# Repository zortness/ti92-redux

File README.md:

# TI-92 Redux
Bringing the TI-92's back to life.

## Intro
My first graphing calculator and introduction to portable programming was an early TI-85.
I became enamoured with the TI calculators in the 90s, longing for a TI-92 when they were
announced, but never able to purchase one. Now, you can find them in various conditions for
relatively cheap on the internet.

Unfortunately, the most common issues seem to be screen related, and the screens on the TI-92
are not easily repaired. Such was the case with one of the TI-92s I purchased, so I began 
thinking about how I could make use of this iconic chasis. 

I found other projects, notably one seen on Hackaday, the 
[TI-92 Revive project](https://hackaday.io/project/175448-reviving-the-ti-92-calculator-into-a-rpi-pc)
and corresponding [github repo](https://github.com/ccadic/TI92-revive). 
This is a cool project in a similar vein, but I wanted to make some different design decisions.

* First, I wanted the PCB to be as simple as possible for the first attempt, trying to keep to a 
2-layer board. 
* Second, I wanted to have the keyboard to be operable as a standalone unit, in case someone wanted
to use it on another project or different SBC than I chose.
* Third, I wanted to re-use as much of the original TI-92 chasis as possible. A goal which I didn't
meet to the original expectation due to the complexity of the original back plates. 

## Physical Replication Strategy
For several parts of this build, I traced the original components (PCB, back plate, etc) onto a 
piece of paper, then scanned them with a flat bed scanner. I then took the drawings and traced 
them into SVG's set to the correct dimensions using InkScape so I could use them with other tools 
such as KiCad and OpenSCAD. I also printed multiple versions of the PCB and various chasis bits 
on my 3D printer to work toward getting the correct fitment with the original chasis pieces.

Most of the SVGs and drawings are included [here](drawings/).

## PCB Design
The PCB is designed in KiCad 7. The board is designed as a custom keyboard, using a Pi Pico (or Pico W)
as the keybord controller. The routing is all done by hand with an attempt at keeping the jumps minimal.

Note: The PCB has tabs and holes to hold an SBC that lines up with the Raspberry Pi mounting holes.

### BOM And Assembly
* 80 count SOD-123 general purpose diode, [1N4148W-TP](https://www.digikey.com/en/products/detail/micro-commercial-co/1N4148W-TP/717196)
* 1 count [RS-282G05A3 tactile switch](https://www.digikey.com/en/products/detail/c-k/RS-282G05A3-SM-RT/2747190)
* 1 count [Pi Pico W](https://www.digikey.com/en/products/detail/raspberry-pi/SC0918/16608263)

I was able to solder all of this with a relatively large soldering iron and some tweezers.
Tin one of the pads for the component first, then heat it up again and set the part on the pad.
Only solder the second pad when you're happy with the alignment.

I used a Raspberry Pi 4 as my SBC.

To pair with the Pi 4, I used the [Pimoroni Hyperpixel 4.0" Touch Display](https://www.adafruit.com/product/3578).
This display is pretty expensive, but I purchased this a while ago, and noticing it seemed to fit perfectly
into the TI-92 chasis is one of the factors that pushed me into completing this project.

A 4" screen of this ratio fits almost perfectly into the TI-92. 

## Printed Pieces
I used OpenSCAD to assemble the designs for printing. Most of the prints are derived from one or 
more SVG drawings, the back plate being the most complicated.

During development, I dropped my keyboard and had to chase keys across the house multiple times. 
I ultimately ended up finding all of my keys, but there is a basic key file included in case you
need to print one.

## Keyboard Software
I chose the [KMK firmware](https://github.com/KMKfw/kmk_firmware) 
(as opposed to something like [QMK](https://docs.qmk.fm/#/) ) mostly due to ease of use and direct
support for the Pi Pico and Pico W. This has the added bonus of being able to easily reprogram the 
keyboard from the finished device itself, using the keyboard itself to make changes.

Follow the instructions for installing the KMK firmware on the device (basically copy most of the
files included in their release). Then drag and drop the [firmware/code.py](firmware/code.py) file
onto the device and it should be ready to go.

## Power Supply
There is no power supply built into this project. For my personal prototype, I'm using a 
[2x18650 container](https://www.digikey.com/en/products/detail/seeed-technology-co-ltd/114090053/10451921)
with a built-in on/off switch into a cheap buck converter. I also attempted to use a L7805 5V
linear regulator, and while it works, even with a heat sink it will get very hot.

I am currently powering the Pi Pico W through the USB cable that connects it to the Pi 4. 

## Development Software
* [KiCad 7](https://www.kicad.org/)
* [InkScape 1.2](https://inkscape.org/)
* [OpenSCAD](http://openscad.org/)
* [KMK Firmware](https://github.com/KMKfw/kmk_firmware)

## Version History

### 2023-05-19 Rev 0
* PCB Rev 0 - Functional 
  * Some mounting hole misalignments that need to be fixed by hand
* KMK Keyboard Firmware - Functional
  * Will work as a USB keyboard on any modern PC
  * Some QoL improvements need to be made on the mouse functionality
  * Really need BlueTooth support to eliminate the USB cable
* Back Plate - Functional
  * Very basic, you can tape or glue power sources to it if so inclined

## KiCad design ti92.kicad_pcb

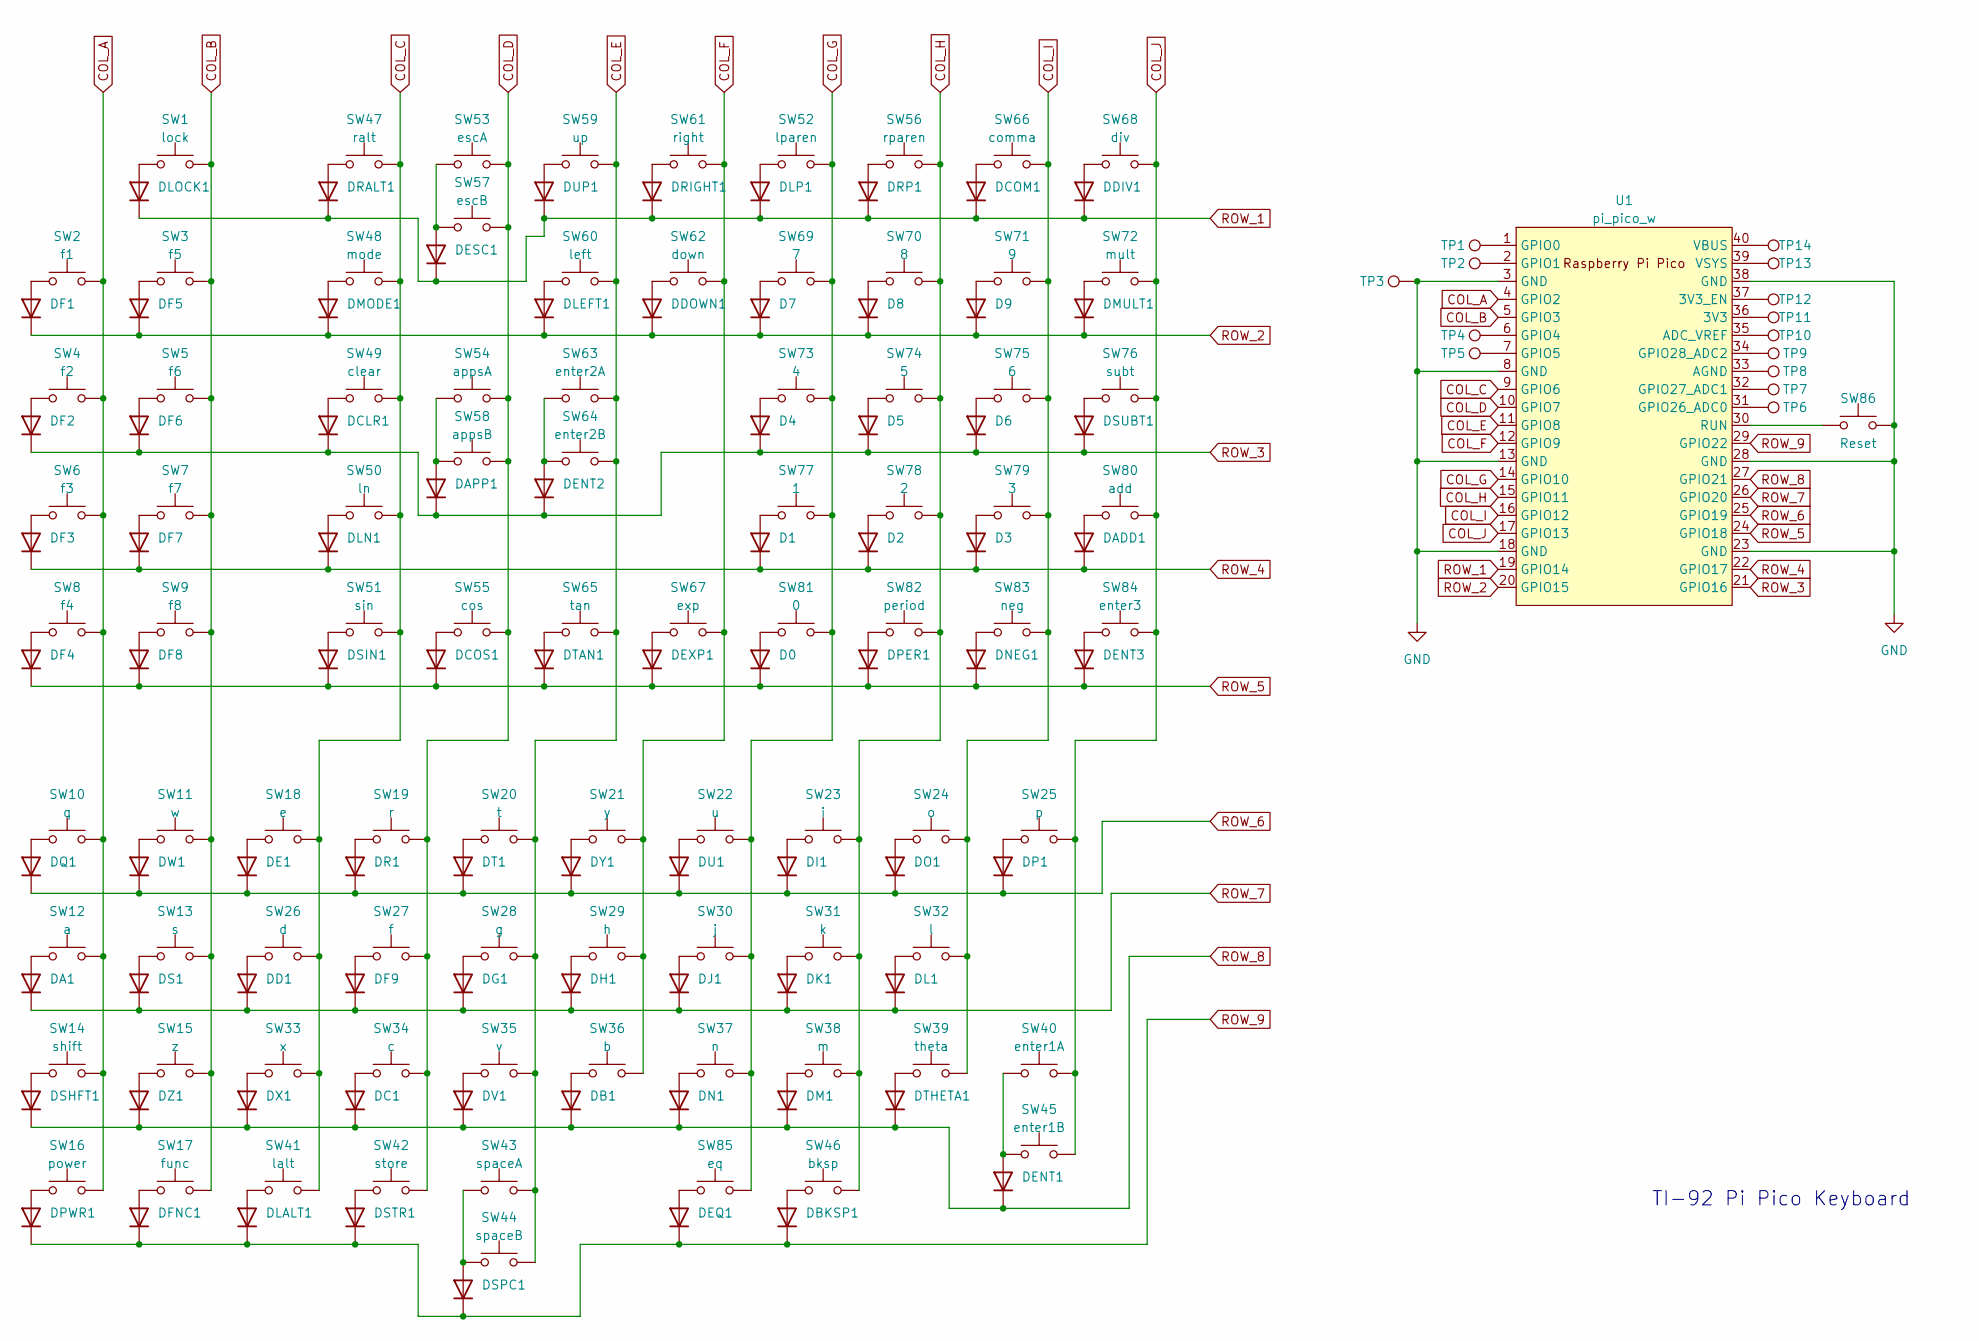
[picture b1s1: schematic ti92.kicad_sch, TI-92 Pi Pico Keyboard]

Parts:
D0, D1, D2, D3, D4, D5, D6, D7, D8, D9: 1N4148W; D_SOD-123
DA1: 1N4148W; D_SOD-123
DADD1: 1N4148W; D_SOD-123
DAPP1: 1N4148W; D_SOD-123
DB1: 1N4148W; D_SOD-123
DBKSP1: 1N4148W; D_SOD-123
DC1: 1N4148W; D_SOD-123
DCLR1: 1N4148W; D_SOD-123
DCOM1: 1N4148W; D_SOD-123
DCOS1: 1N4148W; D_SOD-123
DD1: 1N4148W; D_SOD-123
DDIV1: 1N4148W; D_SOD-123
DDOWN1: 1N4148W; D_SOD-123
DE1: 1N4148W; D_SOD-123
DENT1, DENT2, DENT3: 1N4148W; D_SOD-123
DEQ1: 1N4148W; D_SOD-123
DESC1: 1N4148W; D_SOD-123
DEXP1: 1N4148W; D_SOD-123
DF1, DF2, DF3, DF4, DF5, DF6, DF7, DF8, DF9: 1N4148W; D_SOD-123
DFNC1: 1N4148W; D_SOD-123
DG1: 1N4148W; D_SOD-123
DH1: 1N4148W; D_SOD-123
DI1: 1N4148W; D_SOD-123
DJ1: 1N4148W; D_SOD-123
DK1: 1N4148W; D_SOD-123
DL1: 1N4148W; D_SOD-123
DLALT1: 1N4148W; D_SOD-123
DLEFT1: 1N4148W; D_SOD-123
DLN1: 1N4148W; D_SOD-123
DLOCK1: 1N4148W; D_SOD-123
DLP1: 1N4148W; D_SOD-123
DM1: 1N4148W; D_SOD-123
DMODE1: 1N4148W; D_SOD-123
DMULT1: 1N4148W; D_SOD-123
DN1: 1N4148W; D_SOD-123
DNEG1: 1N4148W; D_SOD-123
DO1: 1N4148W; D_SOD-123
DP1: 1N4148W; D_SOD-123
DPER1: 1N4148W; D_SOD-123
DPWR1: 1N4148W; D_SOD-123
DQ1: 1N4148W; D_SOD-123
DR1: 1N4148W; D_SOD-123
DRALT1: 1N4148W; D_SOD-123
DRIGHT1: 1N4148W; D_SOD-123
DRP1: 1N4148W; D_SOD-123
DS1: 1N4148W; D_SOD-123
DSHFT1: 1N4148W; D_SOD-123
DSIN1: 1N4148W; D_SOD-123
DSPC1: 1N4148W; D_SOD-123
DSTR1: 1N4148W; D_SOD-123
DSUBT1: 1N4148W; D_SOD-123
DT1: 1N4148W; D_SOD-123
DTAN1: 1N4148W; D_SOD-123
DTHETA1: 1N4148W; D_SOD-123
DU1: 1N4148W; D_SOD-123
DUP1: 1N4148W; D_SOD-123
DV1: 1N4148W; D_SOD-123
DW1: 1N4148W; D_SOD-123
DX1: 1N4148W; D_SOD-123
DY1: 1N4148W; D_SOD-123
DZ1: 1N4148W; D_SOD-123
SW1: lock; tibuttonpad
SW2: f1; tibuttonpad
SW3: f5; tibuttonpad
SW4: f2; tibuttonpad
SW5: f6; tibuttonpad
SW6: f3; tibuttonpad
SW7: f7; tibuttonpad
SW8: f4; tibuttonpad
SW9: f8; tibuttonpad
SW10: q; tibuttonpad
SW11: w; tibuttonpad
SW12: a; tibuttonpad
SW13: s; tibuttonpad
SW14: shift; tibuttonpad
SW15: z; tibuttonpad
SW16: power; tibuttonpad
SW17: func; tibuttonpad
SW18: e; tibuttonpad
SW19: r; tibuttonpad
SW20: t; tibuttonpad
SW21: y; tibuttonpad
SW22: u; tibuttonpad
SW23: i; tibuttonpad
SW24: o; tibuttonpad
SW25: p; tibuttonpad
SW26: d; tibuttonpad
SW27: f; tibuttonpad
SW28: g; tibuttonpad
SW29: h; tibuttonpad
SW30: j; tibuttonpad
SW31: k; tibuttonpad
SW32: l; tibuttonpad
SW33: x; tibuttonpad
SW34: c; tibuttonpad
SW35: v; tibuttonpad
SW36: b; tibuttonpad
SW37: n; tibuttonpad
SW38: m; tibuttonpad
SW39: theta; tibuttonpad
SW40: enter1A; tibuttonpad
SW41: lalt; tibuttonpad
SW42: store; tibuttonpad
SW43: spaceA; tibuttonpad
SW44: spaceB; tibuttonpad
SW45: enter1B; tibuttonpad
SW46: bksp; tibuttonpad
SW47: ralt; tibuttonpad
SW48: mode; tibuttonpad
SW49: clear; tibuttonpad
SW50: ln; tibuttonpad
SW51: sin; tibuttonpad
SW52: lparen; tibuttonpad
SW53: escA; tibuttonpad
SW54: appsA; tibuttonpad
SW55: cos; tibuttonpad
SW56: rparen; tibuttonpad
SW57: escB; tibuttonpad
SW58: appsB; tibuttonpad
SW59: up; tibuttonpad
SW60: left; tibuttonpad
SW61: right; tibuttonpad
SW62: down; tibuttonpad
SW63: enter2A; tibuttonpad
SW64: enter2B; tibuttonpad
SW65: tan; tibuttonpad
SW66: comma; tibuttonpad
SW67: exp; tibuttonpad
SW68: div; tibuttonpad
SW69: 7; tibuttonpad
SW70: 8; tibuttonpad
SW71: 9; tibuttonpad
SW72: mult; tibuttonpad
SW73: 4; tibuttonpad
SW74: 5; tibuttonpad
SW75: 6; tibuttonpad
SW76: subt; tibuttonpad
SW77: 1; tibuttonpad
SW78: 2; tibuttonpad
SW79: 3; tibuttonpad
SW80: add; tibuttonpad
SW81: 0; tibuttonpad
SW82: period; tibuttonpad
SW83: neg; tibuttonpad
SW84: enter3; tibuttonpad
SW85: eq; tibuttonpad
SW86: Reset; SW_SPST_CK_RS282G05A3
TP1, TP2, TP3, TP4, TP5, TP6, TP7, TP8, TP9, TP10, TP11, TP12, TP13, TP14: TestPoint_Pad_D1.5mm
U1: pi_pico_w

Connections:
COL_A: SW2.2, SW4.2, SW6.2, SW8.2, SW10.2, SW12.2, SW14.2, SW16.2, U1.4 (GPIO2)
COL_B: SW1.2, SW3.2, SW5.2, SW7.2, SW9.2, SW11.2, SW13.2, SW15.2, SW17.2, U1.5 (GPIO3)
COL_C: SW18.2, SW26.2, SW33.2, SW41.2, SW47.2, SW48.2, SW49.2, SW50.2, SW51.2, U1.9 (GPIO6)
COL_D: SW19.2, SW27.2, SW34.2, SW42.2, SW53.2, SW54.2, SW55.2, SW57.2, SW58.2, U1.10 (GPIO7)
COL_E: SW20.2, SW28.2, SW35.2, SW43.2, SW44.2, SW59.2, SW60.2, SW63.2, SW64.2, SW65.2, U1.11 (GPIO8)
COL_F: SW21.2, SW29.2, SW36.2, SW61.2, SW62.2, SW67.2, U1.12 (GPIO9)
COL_G: SW22.2, SW30.2, SW37.2, SW52.2, SW69.2, SW73.2, SW77.2, SW81.2, SW85.2, U1.14 (GPIO10)
COL_H: SW23.2, SW31.2, SW38.2, SW46.2, SW56.2, SW70.2, SW74.2, SW78.2, SW82.2, U1.15 (GPIO11)
COL_I: SW24.2, SW32.2, SW39.2, SW66.2, SW71.2, SW75.2, SW79.2, SW83.2, U1.16 (GPIO12)
COL_J: SW25.2, SW40.2, SW45.2, SW68.2, SW72.2, SW76.2, SW80.2, SW84.2, U1.17 (GPIO13)
GND: SW86.2, TP3.1, U1.3 (GND), U1.8 (GND), U1.13 (GND), U1.18 (GND), U1.23 (GND), U1.28 (GND), U1.38 (GND)
unnamed: D0.2 (A), SW81.1
unnamed: D1.2 (A), SW77.1
unnamed: D2.2 (A), SW78.1
unnamed: D3.2 (A), SW79.1
unnamed: D4.2 (A), SW73.1
unnamed: D5.2 (A), SW74.1
unnamed: D6.2 (A), SW75.1
unnamed: D7.2 (A), SW69.1
unnamed: D8.2 (A), SW70.1
unnamed: D9.2 (A), SW71.1
unnamed: DA1.2 (A), SW12.1
unnamed: DADD1.2 (A), SW80.1
unnamed: DAPP1.2 (A), SW54.1, SW58.1
unnamed: DB1.2 (A), SW36.1
unnamed: DBKSP1.2 (A), SW46.1
unnamed: DC1.2 (A), SW34.1
unnamed: DCLR1.2 (A), SW49.1
unnamed: DCOM1.2 (A), SW66.1
unnamed: DCOS1.2 (A), SW55.1
unnamed: DD1.2 (A), SW26.1
unnamed: DDIV1.2 (A), SW68.1
unnamed: DDOWN1.2 (A), SW62.1
unnamed: DENT1.2 (A), SW40.1, SW45.1
unnamed: DENT2.2 (A), SW63.1, SW64.1
unnamed: DENT3.2 (A), SW84.1
unnamed: DEQ1.2 (A), SW85.1
unnamed: DESC1.2 (A), SW53.1, SW57.1
unnamed: DEXP1.2 (A), SW67.1
unnamed: DF1.2 (A), SW2.1
unnamed: DF2.2 (A), SW4.1
unnamed: DF3.2 (A), SW6.1
unnamed: DF4.2 (A), SW8.1
unnamed: DF5.2 (A), SW3.1
unnamed: DF6.2 (A), SW5.1
unnamed: DF7.2 (A), SW7.1
unnamed: DF8.2 (A), SW9.1
unnamed: DF9.2 (A), SW27.1
unnamed: DFNC1.2 (A), SW17.1
unnamed: DG1.2 (A), SW28.1
unnamed: DH1.2 (A), SW29.1
unnamed: DI1.2 (A), SW23.1
unnamed: DJ1.2 (A), SW30.1
unnamed: DK1.2 (A), SW31.1
unnamed: DL1.2 (A), SW32.1
unnamed: DLALT1.2 (A), SW41.1
unnamed: DLEFT1.2 (A), SW60.1
unnamed: DLN1.2 (A), SW50.1
unnamed: DLOCK1.2 (A), SW1.1
unnamed: DLP1.2 (A), SW52.1
unnamed: DM1.2 (A), SW38.1
unnamed: DMODE1.2 (A), SW48.1
unnamed: DMULT1.2 (A), SW72.1
unnamed: DN1.2 (A), SW37.1
unnamed: DNEG1.2 (A), SW83.1
unnamed: DO1.2 (A), SW24.1
unnamed: DP1.2 (A), SW25.1
unnamed: DPER1.2 (A), SW82.1
unnamed: DPWR1.2 (A), SW16.1
unnamed: DQ1.2 (A), SW10.1
unnamed: DR1.2 (A), SW19.1
unnamed: DRALT1.2 (A), SW47.1
unnamed: DRIGHT1.2 (A), SW61.1
unnamed: DRP1.2 (A), SW56.1
unnamed: DS1.2 (A), SW13.1
unnamed: DSHFT1.2 (A), SW14.1
unnamed: DSIN1.2 (A), SW51.1
unnamed: DSPC1.2 (A), SW43.1, SW44.1
unnamed: DSTR1.2 (A), SW42.1
unnamed: DSUBT1.2 (A), SW76.1
unnamed: DT1.2 (A), SW20.1
unnamed: DTAN1.2 (A), SW65.1
unnamed: DTHETA1.2 (A), SW39.1
unnamed: DU1.2 (A), SW22.1
unnamed: DUP1.2 (A), SW59.1
unnamed: DV1.2 (A), SW35.1
unnamed: DW1.2 (A), SW11.1
unnamed: DE1.2 (A), SW18.1
unnamed: DX1.2 (A), SW33.1
unnamed: DY1.2 (A), SW21.1
unnamed: DZ1.2 (A), SW15.1
unnamed: TP11.1, U1.36 (3V3)
unnamed: TP12.1, U1.37 (3V3_EN)
unnamed: TP10.1, U1.35 (ADC_VREF)
unnamed: TP8.1, U1.33 (AGND)
unnamed: TP1.1, U1.1 (GPIO0)
unnamed: TP2.1, U1.2 (GPIO1)
unnamed: TP4.1, U1.6 (GPIO4)
unnamed: TP5.1, U1.7 (GPIO5)
unnamed: TP6.1, U1.31 (GPIO26_ADC0)
unnamed: TP7.1, U1.32 (GPIO27_ADC1)
unnamed: TP9.1, U1.34 (GPIO28_ADC2)
unnamed: SW86.1, U1.30 (RUN)
unnamed: TP14.1, U1.40 (VBUS)
unnamed: TP13.1, U1.39 (VSYS)
ROW_1: DCOM1.1 (K), DDIV1.1 (K), DESC1.1 (K), DLOCK1.1 (K), DLP1.1 (K), DRALT1.1 (K), DRIGHT1.1 (K), DRP1.1 (K), DUP1.1 (K), U1.19 (GPIO14)
ROW_2: D7.1 (K), D8.1 (K), D9.1 (K), DDOWN1.1 (K), DF1.1 (K), DF5.1 (K), DLEFT1.1 (K), DMODE1.1 (K), DMULT1.1 (K), U1.20 (GPIO15)
ROW_3: D4.1 (K), D5.1 (K), D6.1 (K), DAPP1.1 (K), DCLR1.1 (K), DENT2.1 (K), DF2.1 (K), DF6.1 (K), DSUBT1.1 (K), U1.21 (GPIO16)
ROW_4: D1.1 (K), D2.1 (K), D3.1 (K), DADD1.1 (K), DF3.1 (K), DF7.1 (K), DLN1.1 (K), U1.22 (GPIO17)
ROW_5: D0.1 (K), DCOS1.1 (K), DENT3.1 (K), DEXP1.1 (K), DF4.1 (K), DF8.1 (K), DNEG1.1 (K), DPER1.1 (K), DSIN1.1 (K), DTAN1.1 (K), U1.24 (GPIO18)
ROW_6: DE1.1 (K), DI1.1 (K), DO1.1 (K), DP1.1 (K), DQ1.1 (K), DR1.1 (K), DT1.1 (K), DU1.1 (K), DW1.1 (K), DY1.1 (K), U1.25 (GPIO19)
ROW_7: DA1.1 (K), DD1.1 (K), DF9.1 (K), DG1.1 (K), DH1.1 (K), DJ1.1 (K), DK1.1 (K), DL1.1 (K), DS1.1 (K), U1.26 (GPIO20)
ROW_8: DB1.1 (K), DC1.1 (K), DENT1.1 (K), DM1.1 (K), DN1.1 (K), DSHFT1.1 (K), DTHETA1.1 (K), DV1.1 (K), DX1.1 (K), DZ1.1 (K), U1.27 (GPIO21)
ROW_9: DBKSP1.1 (K), DEQ1.1 (K), DFNC1.1 (K), DLALT1.1 (K), DPWR1.1 (K), DSPC1.1 (K), DSTR1.1 (K), U1.29 (GPIO22)

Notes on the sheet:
TI-92 Pi Pico Keyboard

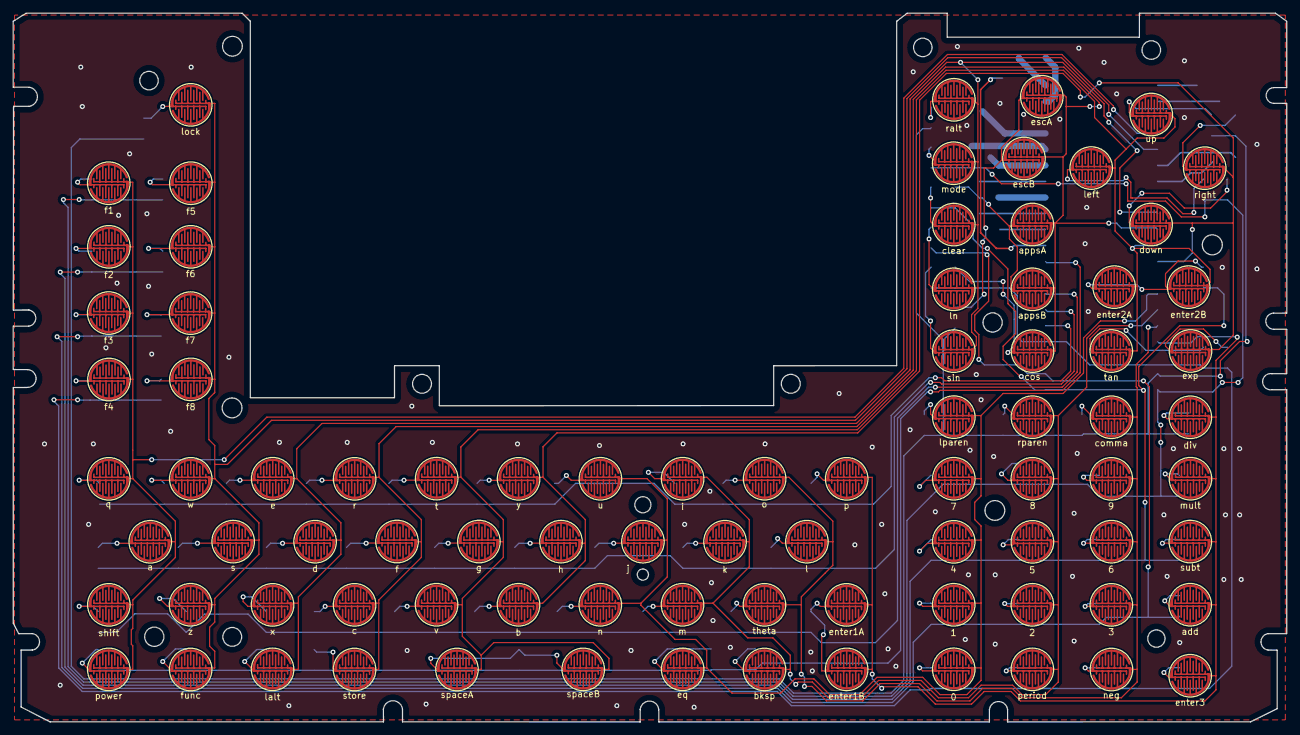
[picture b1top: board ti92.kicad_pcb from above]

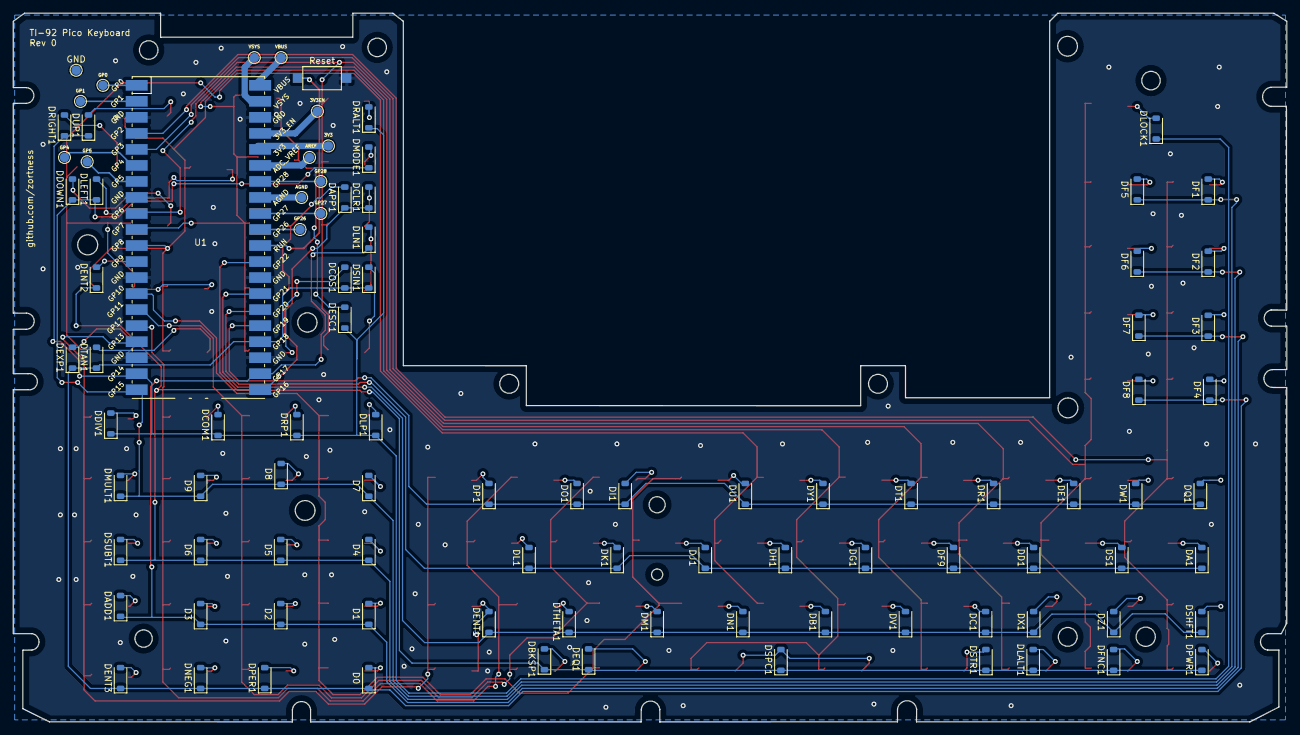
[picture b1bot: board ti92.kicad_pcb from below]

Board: 2 copper layers, 201.9 x 112.4 mm, 181 parts (96 on the bottom side), 114 nets.

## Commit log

2023-05-19 import of files and initial documentation
2023-05-19 testing image fix for readme
2023-05-19 fixing image display on another readme
2023-05-20 updating keyboard firmware
    Working on issues/1 ; Toggle for mouse functions. Adding ALT key on power button for normal layers.
